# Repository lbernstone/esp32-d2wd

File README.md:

# esp32-d2wd
A barebones and small module design for esp32-d2wd including a PCB antenna.
This design does not expose all the GPIO pins, only 19 of them.

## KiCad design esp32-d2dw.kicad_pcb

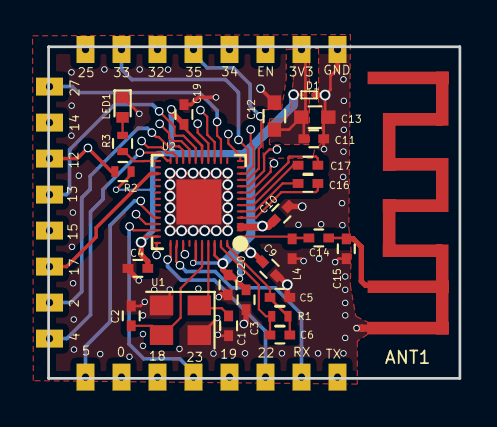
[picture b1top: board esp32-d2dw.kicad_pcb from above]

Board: 4 copper layers, 22.8 x 18.4 mm, 32 parts (0 on the bottom side), 36 nets.

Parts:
ANT1: PCB_ANT; PCB_Antenna_2_4_GHz_ESP32
C1, C2: 22pF; C_0402
C3: 100pF; C_0402
C4, C9, C10, C19: 0.1; C_0402
C5: 10nF; C_0402
C6: 3.3nF; C_0402
C11, C20: 1; C_0402
C12, C13: 10; C_0603
C14: 3.9pF; C_0402
C15: 2.4pF; C_0402
C16, C17: 270pF; C_0402
D1: PESD5V0R1BSFYL; SOD962-2
J1, J4, J6: CONN_01X02; Module_Conn_SMT_2x
J2, J3, J5: CONN_01X06; Module_Conn_SMT_6x
L4: 2.7nH; C_0402_NoSilk
LED1: 2.3V/30mA; LED_0402
R1, R2: 20K; R_0402
R3: 40; R_0402
U1: 40MHz +/- 10ppm; Oscillator_SMD_Abracon_ASE-4pin_3.2x2.5mm
U2: ESP32; ESP32-QFN48

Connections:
+3V3: C3.2, C4.1, C9.1, C10.2, C11.1, C12.1, C13.1, C19.2, C20.2, D1.1, J1.2, R2.1, U2.1, U2.3, U2.4, U2.19, U2.37, U2.43, U2.46
GND: ANT1.2, C1.2, C2.2, C3.1, C4.2, C5.1, C9.2, C10.1, C11.2, C12.2, C13.2, C15.2, C19.1, C20.1, D1.2, J1.1, L4.1, LED1.1, U1.2, U1.4, U2.49
unnamed: ANT1.1, C14.1, C15.1
unnamed: C1.1, U1.1, U2.45
unnamed: C2.1, U1.3, U2.44
unnamed: C5.2, C6.2, R1.2, U2.48
unnamed: C6.1, R1.1, U2.47
unnamed: C14.2, L4.2, U2.2
unnamed: C16.1, U2.5
unnamed: C16.2, U2.6
unnamed: C17.1, U2.7
unnamed: C17.2, U2.8
unnamed: J2.1, U2.9
unnamed: J2.2, U2.10
unnamed: J2.3, U2.11
unnamed: J2.4, U2.12
unnamed: J2.5, U2.13
unnamed: J2.6, U2.14
unnamed: J3.1, U2.16
unnamed: J3.2, U2.17
unnamed: J3.3, R2.2, U2.18
unnamed: J3.4, U2.20
unnamed: J3.5, U2.21
unnamed: J3.6, U2.27
unnamed: J4.1, U2.22
unnamed: J4.2, U2.24
unnamed: J5.1, U2.34
unnamed: J5.2, U2.23
unnamed: J5.3, U2.35
unnamed: J5.4, U2.36
unnamed: J5.5, U2.38
unnamed: J5.6, U2.39
unnamed: J6.1, U2.40
unnamed: J6.2, U2.41
unnamed: LED1.2, R3.1
unnamed: R3.2, U2.25

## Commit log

2017-09-05 Added part #s to BOM.csv
2017-09-14 Fully stitched with 2mm pitch connectors
2017-10-13 Changed to 19 GPIO pins
2017-10-13 needed to have fills redrawn
2017-12-28 added kicad image
2017-12-28 fixed image address
